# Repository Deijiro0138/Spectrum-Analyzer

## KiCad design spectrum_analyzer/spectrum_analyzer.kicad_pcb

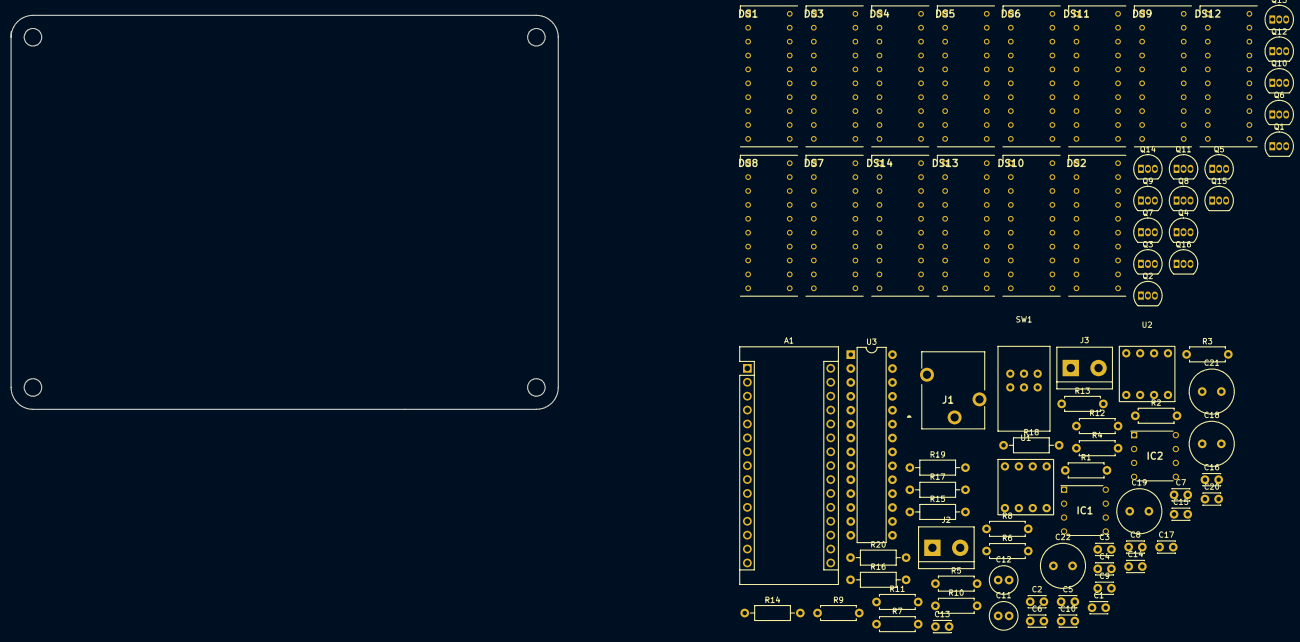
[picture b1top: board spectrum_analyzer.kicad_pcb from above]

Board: 2 copper layers, 100.0 x 72.0 mm, 82 parts (0 on the bottom side), 82 nets, no tracks yet.

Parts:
A1: Arduino_Nano_v3.x; Arduino_Nano
C1, C3: 33p; C_Disc_D3.0mm_W2.0mm_P2.50mm
C2, C4: 0.01u; C_Disc_D3.0mm_W2.0mm_P2.50mm
C5, C6, C7, C8, C15, C16, C17, C20: 0.1u; C_Disc_D3.0mm_W2.0mm_P2.50mm
C9, C10: 330p; C_Disc_D3.0mm_W2.0mm_P2.50mm
C11, C12: 2.2u; C_Radial_D5.0mm_H11.0mm_P2.00mm
C13, C14: 10u; C_Disc_D3.0mm_W2.0mm_P2.50mm
C18, C19, C21, C22: 470u; C_Radial_D8.0mm_H7.0mm_P3.50mm
DS1, DS2, DS3, DS4, DS5, DS6, DS7, DS8, DS9, DS10, DS11, DS12, DS13, DS14: OSX10201-GYR1; DIPS760W45P254L2550H815Q20N
IC1, IC2: NJM386BD; DIP762W56P254L880H425Q8N
J1: MJ352W-0; MJ352W0
J2, J3: Conn_01x02_Male; TerminalBlock_bornier-2_P5.08mm
Q1, Q2, Q3, Q4, Q5, Q6, Q7, Q8, Q9, Q10, Q11, Q12, Q13, Q14, Q15, Q16: 2SA1015; TO-92_Inline
R1, R2: 22k; R_Axial_DIN0207_L6.3mm_D2.5mm_P7.62mm_Horizontal
R3, R4: 200k; R_Axial_DIN0207_L6.3mm_D2.5mm_P7.62mm_Horizontal
R5, R6: 10k; R_Axial_DIN0207_L6.3mm_D2.5mm_P7.62mm_Horizontal
R7, R8, R13: 1k; R_Axial_DIN0207_L6.3mm_D2.5mm_P7.62mm_Horizontal
R9, R10: 50k; R_Axial_DIN0207_L6.3mm_D2.5mm_P7.62mm_Horizontal
R11, R12: 10; R_Axial_DIN0207_L6.3mm_D2.5mm_P7.62mm_Horizontal
R14, R15, R16, R17, R18, R19, R20: 100; R_Axial_DIN0207_L6.3mm_D2.5mm_P10.16mm_Horizontal
SW1: RK0972B103L15F; RK0971220-F15-C0-A103
U1, U2: MSGEQ7; 2227MC-08-03
U3: TLC5940NT; DIP-28_W7.62mm

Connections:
/1: R14.2, U3.12
/2: R15.2, U3.13
/3: R16.2, U3.14
/4: R17.2, U3.15
/5: A1.5, R18.2
/5V: A1.27, C5.2, C6.2, C17.2, C18.1, C20.2, C21.1, IC1.6, IC2.6, Q1.1, Q2.1, R3.1, R4.1, U1.1, U2.1, U3.19, U3.21
/6: A1.9, R19.2
/7: A1.10, R20.2
/D3: A1.6, U3.18
/D9: A1.12, U3.24
/D10: A1.13, U3.23
/D11: A1.14, U3.26
/D13: A1.16, U3.25
/L: Q2.3, U3.11
/L_Bolume: C12.2, SW1.2
/R: Q1.3, U3.10
/R_Bolume: C11.2, SW1.5
/audio_in_l: J1.3, R1.2, SW1.1
/audio_in_r: J1.2, R2.2, SW1.4
/cathode_A_g1: DS1.20, DS2.20, DS3.20, DS4.20, DS5.20, DS6.20, DS7.20, DS8.20, DS9.20, DS10.20, DS11.20, DS12.20, DS13.20, DS14.20, U3.28
/cathode_B_g2: DS1.19, DS2.19, DS3.19, DS4.19, DS5.19, DS6.19, DS7.19, DS8.19, DS9.19, DS10.19, DS11.19, DS12.19, DS13.19, DS14.19, U3.1
/cathode_C_g3: DS1.18, DS2.18, DS3.18, DS4.18, DS5.18, DS6.18, DS7.18, DS8.18, DS9.18, DS10.18, DS11.18, DS12.18, DS13.18, DS14.18, U3.2
/cathode_D_g4: DS1.17, DS2.17, DS3.17, DS4.17, DS5.17, DS6.17, DS7.17, DS8.17, DS9.17, DS10.17, DS11.17, DS12.17, DS13.17, DS14.17, U3.3
/cathode_E_g5: DS1.16, DS2.16, DS3.16, DS4.16, DS5.16, DS6.16, DS7.16, DS8.16, DS9.16, DS10.16, DS11.16, DS12.16, DS13.16, DS14.16, U3.4
/cathode_F_y1: DS1.15, DS2.15, DS3.15, DS4.15, DS5.15, DS6.15, DS7.15, DS8.15, DS9.15, DS10.15, DS11.15, DS12.15, DS13.15, DS14.15, U3.5
/cathode_G_y2: DS1.14, DS2.14, DS3.14, DS4.14, DS5.14, DS6.14, DS7.14, DS8.14, DS9.14, DS10.14, DS11.14, DS12.14, DS13.14, DS14.14, U3.6
/cathode_H_y3: DS1.13, DS2.13, DS3.13, DS4.13, DS5.13, DS6.13, DS7.13, DS8.13, DS9.13, DS10.13, DS11.13, DS12.13, DS13.13, DS14.13, U3.7
/cathode_I_r1: DS1.12, DS2.12, DS3.12, DS4.12, DS5.12, DS6.12, DS7.12, DS8.12, DS9.12, DS10.12, DS11.12, DS12.12, DS13.12, DS14.12, U3.8
/cathode_J_r2: DS1.11, DS2.11, DS3.11, DS4.11, DS5.11, DS6.11, DS7.11, DS8.11, DS9.11, DS10.11, DS11.11, DS12.11, DS13.11, DS14.11, U3.9
/data_out_l: A1.19, U1.3
/data_out_r: A1.20, U2.3
/led/1: Q3.3, Q4.3, R14.1
/led/2: Q5.3, Q6.3, R15.1
/led/3: Q7.3, Q8.3, R16.1
/led/4: Q9.3, Q10.3, R17.1
/led/5: Q11.3, Q12.3, R18.1
/led/6: Q13.3, Q14.3, R19.1
/led/7: Q15.3, Q16.3, R20.1
/led/L1: DS2.1, DS2.2, DS2.3, DS2.4, DS2.5, DS2.6, DS2.7, DS2.8, DS2.9, DS2.10, Q4.2
/led/L2: DS4.1, DS4.2, DS4.3, DS4.4, DS4.5, DS4.6, DS4.7, DS4.8, DS4.9, DS4.10, Q6.2
/led/L3: DS6.1, DS6.2, DS6.3, DS6.4, DS6.5, DS6.6, DS6.7, DS6.8, DS6.9, DS6.10, Q8.2
/led/L4: DS8.1, DS8.2, DS8.3, DS8.4, DS8.5, DS8.6, DS8.7, DS8.8, DS8.9, DS8.10, Q10.2
/led/L5: DS10.1, DS10.2, DS10.3, DS10.4, DS10.5, DS10.6, DS10.7, DS10.8, DS10.9, DS10.10, Q12.2
/led/L6: DS12.1, DS12.2, DS12.3, DS12.4, DS12.5, DS12.6, DS12.7, DS12.8, DS12.9, DS12.10, Q14.2
/led/L7: DS14.1, DS14.2, DS14.3, DS14.4, DS14.5, DS14.6, DS14.7, DS14.8, DS14.9, DS14.10, Q16.2
/led/R1: DS1.1, DS1.2, DS1.3, DS1.4, DS1.5, DS1.6, DS1.7, DS1.8, DS1.9, DS1.10, Q3.2
/led/R2: DS3.1, DS3.2, DS3.3, DS3.4, DS3.5, DS3.6, DS3.7, DS3.8, DS3.9, DS3.10, Q5.2
/led/R3: DS5.1, DS5.2, DS5.3, DS5.4, DS5.5, DS5.6, DS5.7, DS5.8, DS5.9, DS5.10, Q7.2
/led/R4: DS7.1, DS7.2, DS7.3, DS7.4, DS7.5, DS7.6, DS7.7, DS7.8, DS7.9, DS7.10, Q9.2
/led/R5: DS9.1, DS9.2, DS9.3, DS9.4, DS9.5, DS9.6, DS9.7, DS9.8, DS9.9, DS9.10, Q11.2
/led/R6: DS11.1, DS11.2, DS11.3, DS11.4, DS11.5, DS11.6, DS11.7, DS11.8, DS11.9, DS11.10, Q13.2
/led/R7: DS13.1, DS13.2, DS13.3, DS13.4, DS13.5, DS13.6, DS13.7, DS13.8, DS13.9, DS13.10, Q15.2
/reset: A1.8, U1.7, U2.7
/strobe: A1.7, U1.4, U2.4
GND: A1.4, A1.29, C1.2, C3.2, C5.1, C6.1, C7.1, C8.1, C9.2, C10.2, C17.1, C18.2, C20.1, C21.2, IC1.4, IC2.4, J1.1, J2.2, J3.2, R5.2, R6.2, R11.2, R12.2, R13.2, SW1.3, SW1.6, U1.2, U2.2, U3.22, U3.27
unnamed: C1.1, R3.2, U1.8
unnamed: C2.1, U1.5
unnamed: C2.2, R1.1
unnamed: C3.1, R4.2, U2.8
unnamed: C4.1, U2.5
unnamed: C4.2, R2.1
unnamed: C7.2, U1.6
unnamed: C8.2, U2.6
unnamed: C9.1, IC1.3, R7.1
unnamed: C10.1, IC2.3, R8.1
unnamed: C11.1, R7.2
unnamed: C12.1, R8.2
unnamed: C13.1, C15.1, C19.1, IC1.5
unnamed: C13.2, R9.1
unnamed: C14.1, C16.1, C22.1, IC2.5
unnamed: C14.2, R10.1
unnamed: C15.2, R11.1
unnamed: C16.2, R12.1
unnamed: C19.2, J2.1
unnamed: C22.2, J3.1
unnamed: IC1.1, R9.2
unnamed: IC1.2, R5.1
unnamed: IC2.1, R10.2
unnamed: IC2.2, R6.1
unnamed: Q1.2, Q3.1, Q5.1, Q7.1, Q9.1, Q11.1, Q13.1, Q15.1
unnamed: Q2.2, Q4.1, Q6.1, Q8.1, Q10.1, Q12.1, Q14.1, Q16.1
unnamed: R13.1, U3.20
